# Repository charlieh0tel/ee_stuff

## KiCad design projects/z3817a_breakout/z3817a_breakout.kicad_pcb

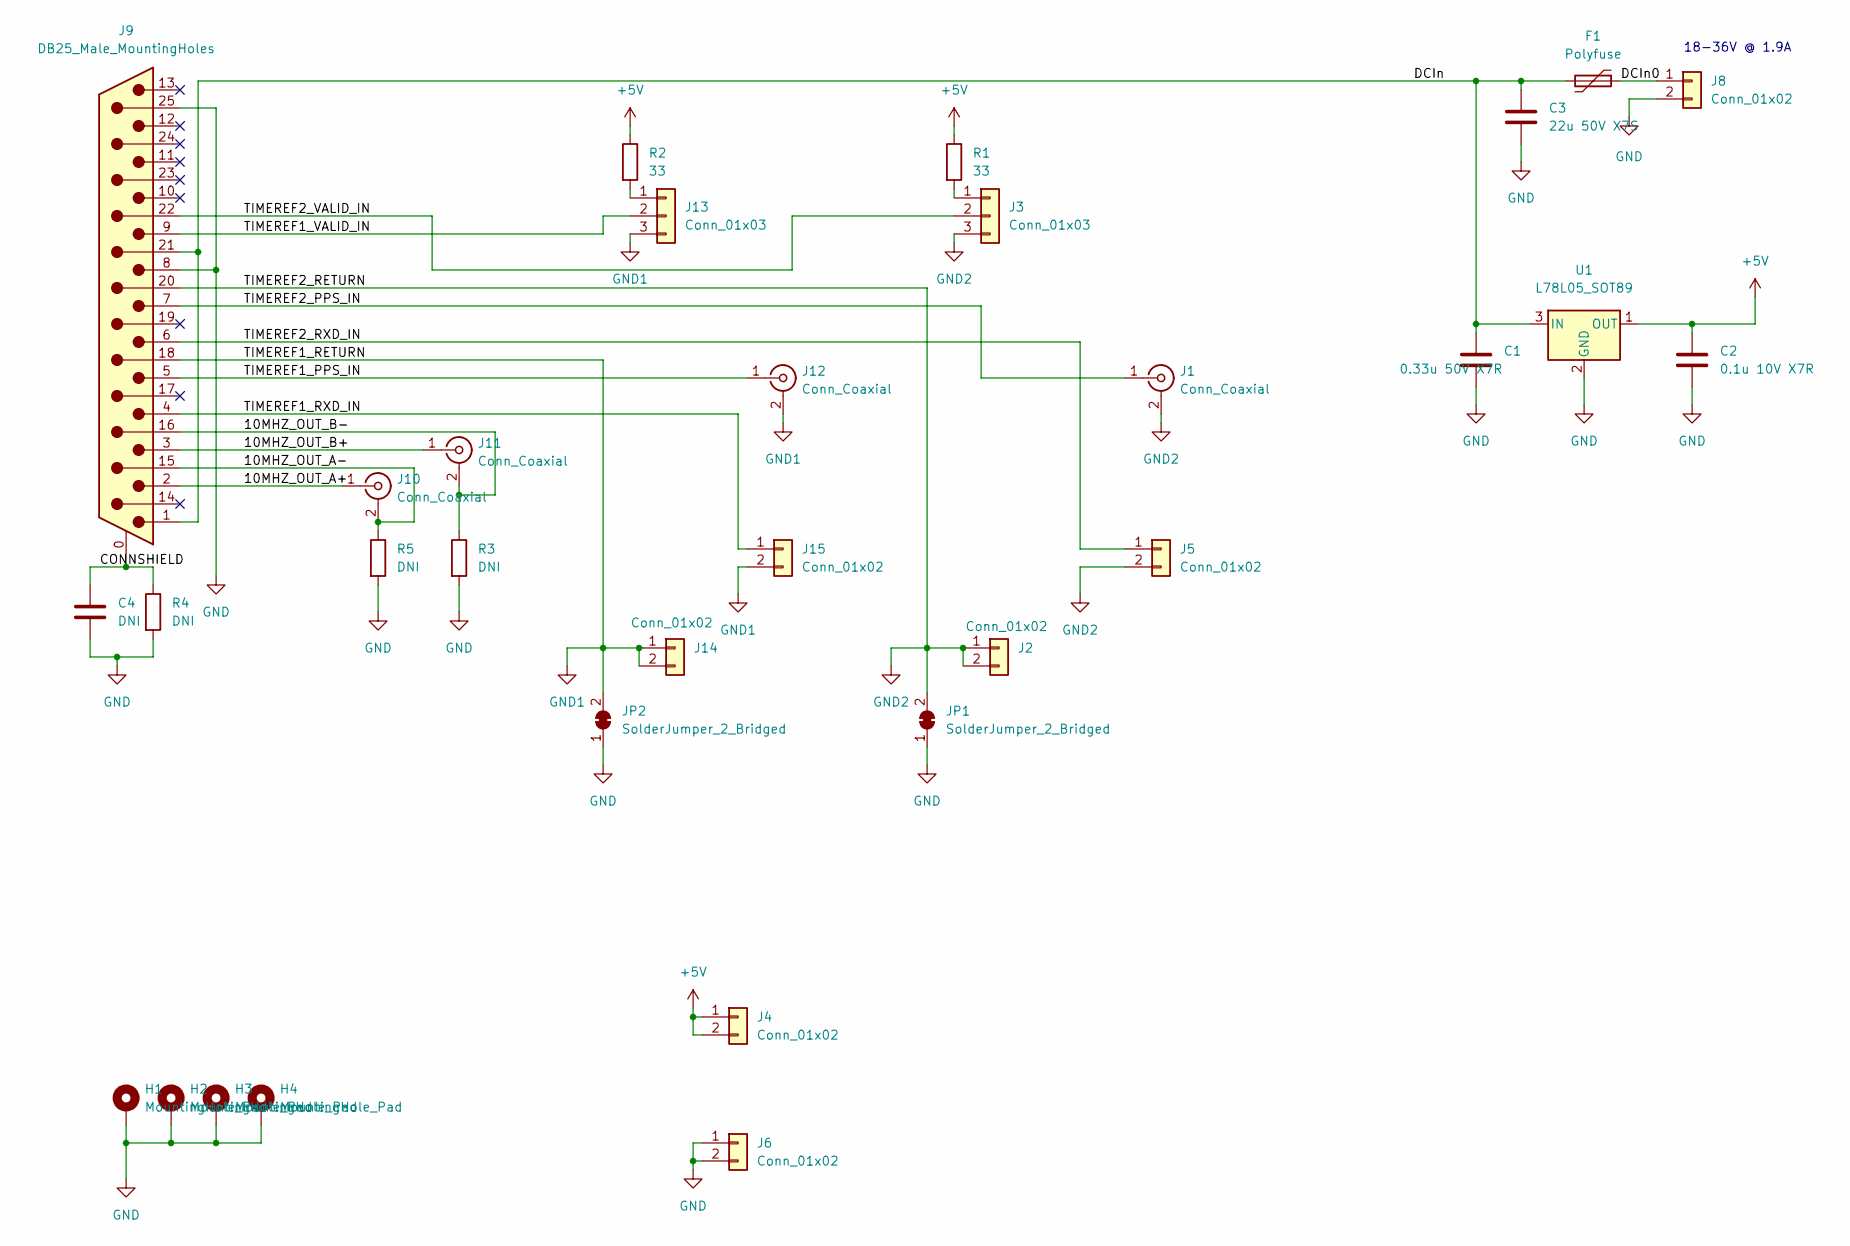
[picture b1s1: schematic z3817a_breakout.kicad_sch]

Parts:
C1: 0.33u 50V X7R; C_0805_2012Metric_Pad1.18x1.45mm_HandSolder
C2: 0.1u 10V X7R; C_0805_2012Metric_Pad1.18x1.45mm_HandSolder
C3: 22u 50V X7S; C_2220_5650Metric_Pad1.97x5.40mm_HandSolder
C4: DNI; C_0805_2012Metric_Pad1.18x1.45mm_HandSolder
F1: Polyfuse; Fuse_2920_7451Metric_Pad2.10x5.45mm_HandSolder
H1, H2, H3, H4: MountingHole_Pad; MountingHole_3.2mm_M3_ISO7380_Pad
J1, J10, J11, J12: Conn_Coaxial; SMA_Molex_73251-2200_Horizontal
J2, J4, J5, J6, J14, J15: Conn_01x02; PinHeader_1x02_P2.54mm_Vertical
J3, J13: Conn_01x03; PinHeader_1x03_P2.54mm_Vertical
J8: Conn_01x02; PhoenixContact_MSTBA_2,5_2-G-5,08_1x02_P5.08mm_Horizontal
J9: DB25_Male_MountingHoles; DSUB-25_Female_Horizontal_P2.77x2.84mm_EdgePinOffset7.70mm_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
JP1, JP2: SolderJumper_2_Bridged; SolderJumper-2_P1.3mm_Bridged_RoundedPad1.0x1.5mm
R1, R2: 33; R_0603_1608Metric_Pad0.98x0.95mm_HandSolder
R3, R4, R5: DNI; R_0603_1608Metric_Pad0.98x0.95mm_HandSolder
U1: L78L05_SOT89; SOT-89-3

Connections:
+5V: C2.1, J4.1, J4.2, R1.1, R2.1, U1.1 (OUT)
/10MHZ_OUT_A+: J9.2, J10.1 (In)
/10MHZ_OUT_A-: J9.15, J10.2 (Ext), R5.1
/10MHZ_OUT_B+: J9.3, J11.1 (In)
/10MHZ_OUT_B-: J9.16, J11.2 (Ext), R3.1
/CONNSHIELD: C4.1, J9.0 (PAD), R4.1
/DCIn: C1.1, C3.1, F1.2, J9.1, J9.21, U1.3 (IN)
/DCIn0: F1.1, J8.1
/TIMEREF1_PPS_IN: J9.5, J12.1 (In)
/TIMEREF1_RXD_IN: J9.4, J15.1
/TIMEREF1_VALID_IN: J9.9, J13.2
/TIMEREF2_PPS_IN: J1.1 (In), J9.7
/TIMEREF2_RXD_IN: J5.1, J9.6
/TIMEREF2_VALID_IN: J3.2, J9.22
GND: C1.2, C2.2, C3.2, C4.2, H1.1, H2.1, H3.1, H4.1, J6.1, J6.2, J8.2, J9.8, J9.25, JP1.1 (A), JP2.1 (A), R3.2, R4.2, R5.2, U1.2 (GND)
GND1: J9.18, J12.2 (Ext), J13.3, J14.1, J14.2, J15.2, JP2.2 (B)
GND2: J1.2 (Ext), J2.1, J2.2, J3.3, J5.2, J9.20, JP1.2 (B)
unnamed: J3.1, R1.2
unnamed: J13.1, R2.2

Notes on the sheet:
18-36V @ 1.9A

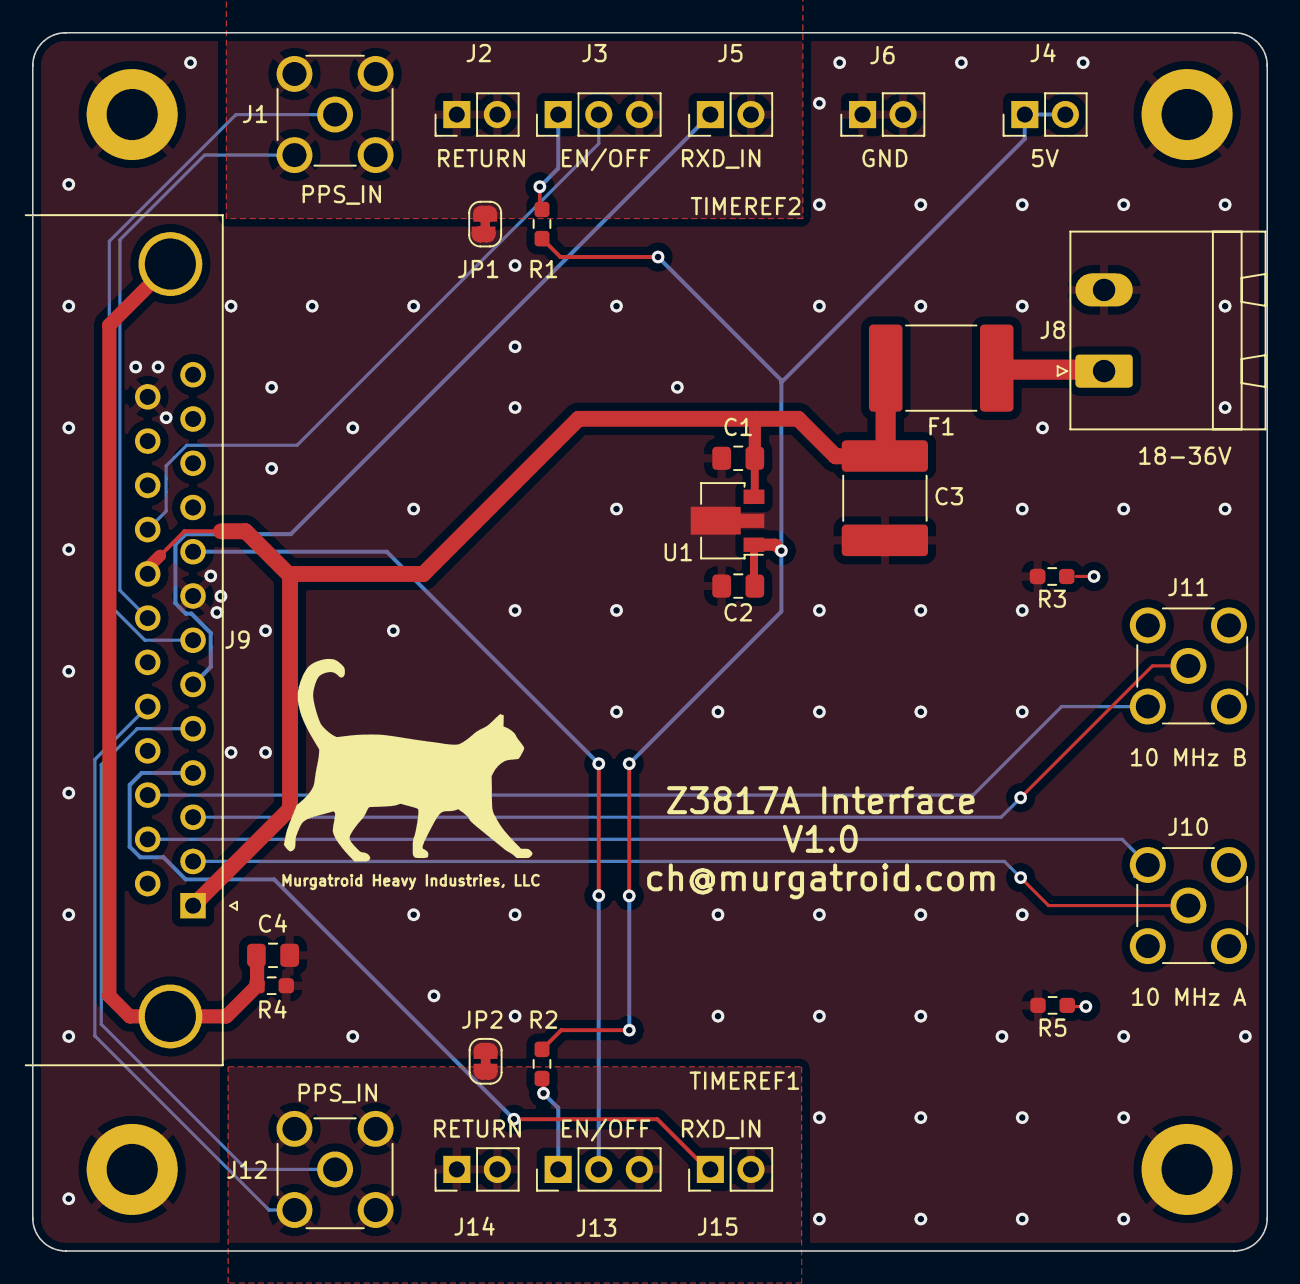
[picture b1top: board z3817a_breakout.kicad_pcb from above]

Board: 2 copper layers, 77.3 x 76.3 mm, 31 parts (0 on the bottom side), 19 nets.

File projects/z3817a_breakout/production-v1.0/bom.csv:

Designator,Footprint,Quantity,Value,LCSC Part #
C1,0805,1,0.33u 50V X7R,
C2,0805,1,0.1u 10V X7R,
C3,2220,1,22u 50V X7S,
C4,0805,1,DNI,
F1,2920,1,Polyfuse,
"H1, H2, H3, H4",MountingHole_3.2mm_M3_ISO7380_Pad,4,MountingHole_Pad,
"J1, J10, J11, J12",SMA_Molex_73251-2200_Horizontal,4,Conn_Coaxial,
"J13, J3",PinHeader_1x03_P2.54mm_Vertical,2,Conn_01x03,
"J14, J15, J2, J4, J5, J6",PinHeader_1x02_P2.54mm_Vertical,6,Conn_01x02,
J8,"PhoenixContact_MSTBA_2,5_2-G-5,08_1x02_P5.08mm_Horizontal",1,Conn_01x02,
J9,DSUB-25_Female_Horizontal_P2.77x2.84mm_EdgePinOffset7.70mm_Housed_MountingHolesOffset9.12mm,1,DB25_Male_MountingHoles,
"JP1, JP2",SolderJumper-2_P1.3mm_Bridged_RoundedPad1.0x1.5mm,2,SolderJumper_2_Bridged,
"R1, R2",0603,2,33,
"R3, R4, R5",0603,3,DNI,
U1,SOT-89-3,1,L78L05_SOT89,

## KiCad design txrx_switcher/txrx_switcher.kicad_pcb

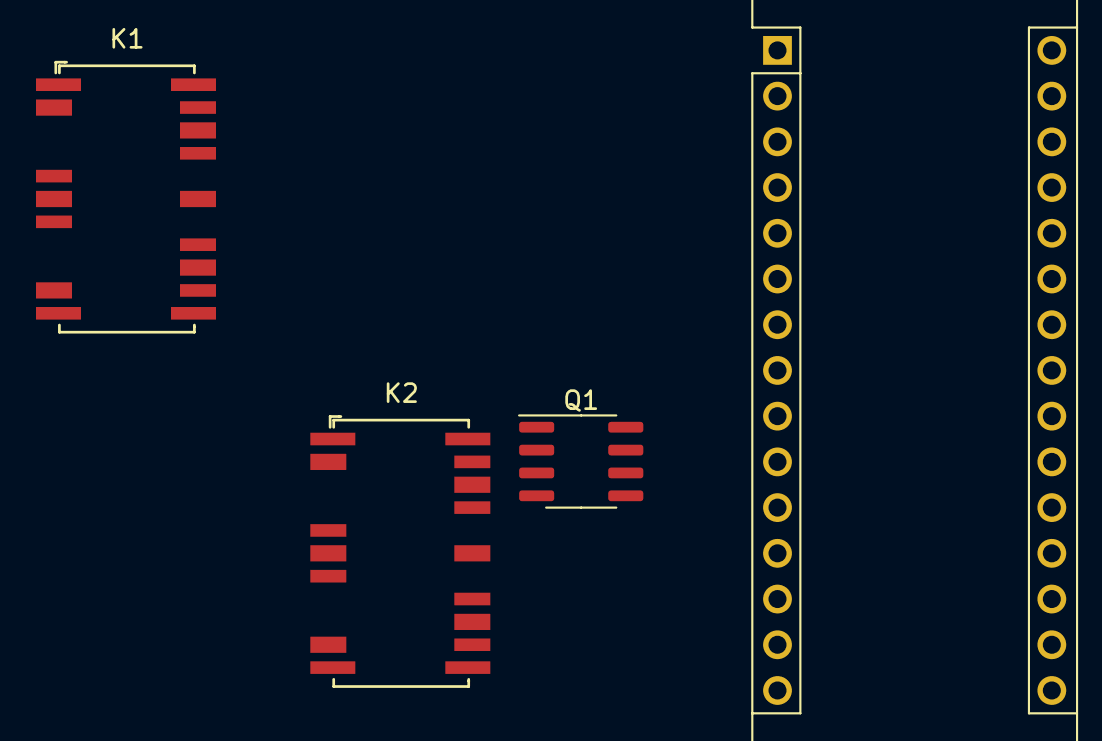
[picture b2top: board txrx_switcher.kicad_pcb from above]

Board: 2 copper layers, 4 parts (0 on the bottom side), 4 nets, no tracks yet.

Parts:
A1: Arduino_Nano_v3.x; Arduino_Nano
K1, K2: HF3-56; Relay_SPDT_AXICOM_HF3Series_50ohms_Pitch1.27mm
Q1: IRF7309IPBF; SOIC-8_3.9x4.9mm_P1.27mm

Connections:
+VDC: K1.1, K2.1
GND: K1.2 (GND), K1.5 (GND), K1.7 (GND), K1.10 (GND), K1.12 (GND), K1.13 (GND), K1.15 (GND), K1.17 (GND), K1.19 (GND), K1.21 (GND), K1.22 (GND), K2.2 (GND), K2.5 (GND), K2.7 (GND), K2.10 (GND), K2.12 (GND), K2.13 (GND), K2.15 (GND), K2.17 (GND), K2.19 (GND), K2.21 (GND), K2.22 (GND), Q1.1 (S)
unnamed: K1.11, K2.11, Q1.7 (D), Q1.8 (D)
unnamed: K1.20, K2.20
